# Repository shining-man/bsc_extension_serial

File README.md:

# Serial port extension for the BSC
This extension adds 8 additional serial ports to the Battery safety controller (BSC). This allows a total of 11 serial devices to be connected to the BSC.

The BSC is connected to this extension via an 8-pin bus cable.

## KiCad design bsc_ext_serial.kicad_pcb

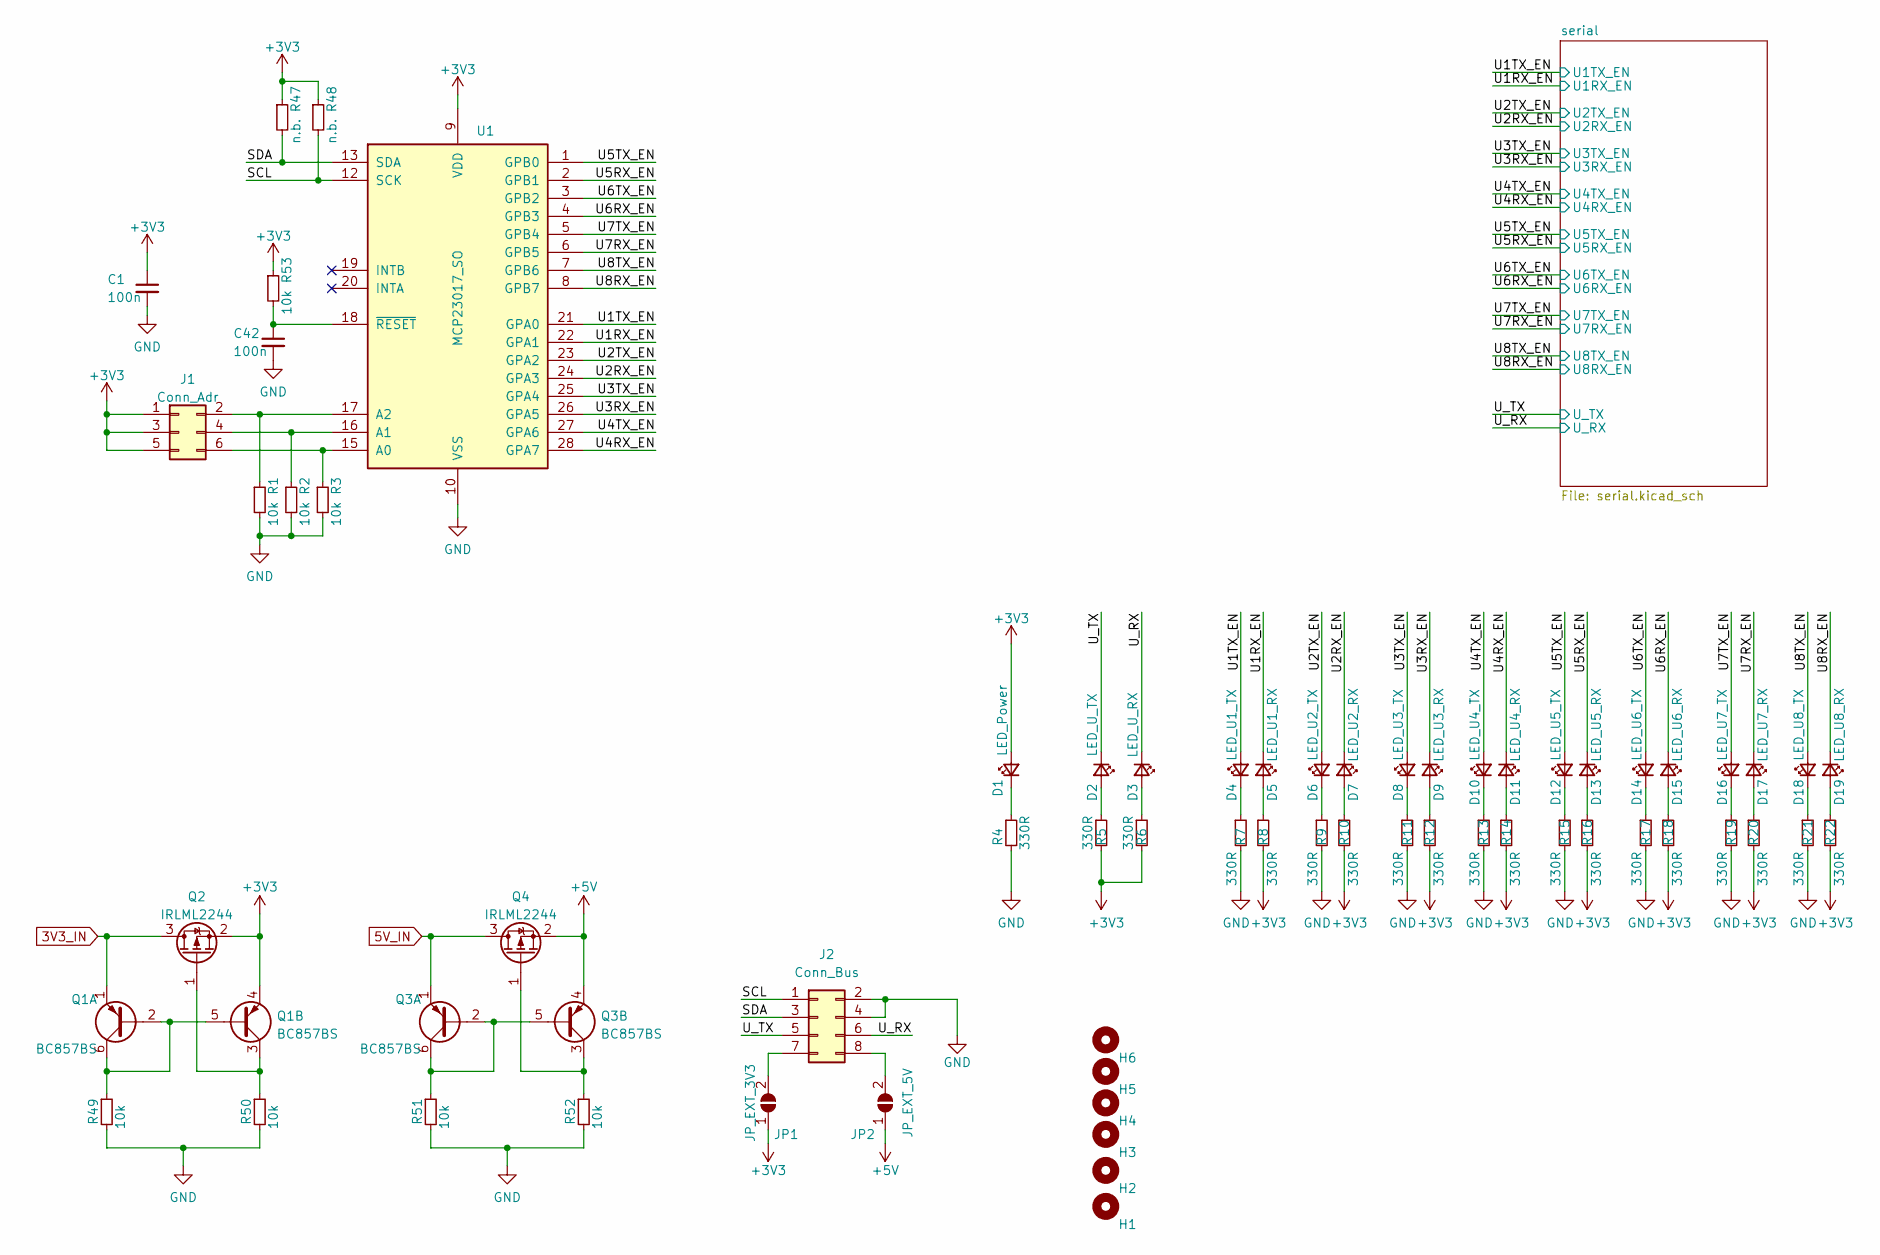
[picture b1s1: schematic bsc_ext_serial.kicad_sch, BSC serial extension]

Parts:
C1, C42: 100n; C_0603_1608Metric
D1: LED_Power; LED_0603_1608Metric
D2: LED_U_TX; LED_0603_1608Metric
D3: LED_U_RX; LED_0603_1608Metric
D4: LED_U1_TX; LED_0603_1608Metric
D5: LED_U1_RX; LED_0603_1608Metric
D6: LED_U2_TX; LED_0603_1608Metric
D7: LED_U2_RX; LED_0603_1608Metric
D8: LED_U3_TX; LED_0603_1608Metric
D9: LED_U3_RX; LED_0603_1608Metric
D10: LED_U4_TX; LED_0603_1608Metric
D11: LED_U4_RX; LED_0603_1608Metric
D12: LED_U5_TX; LED_0603_1608Metric
D13: LED_U5_RX; LED_0603_1608Metric
D14: LED_U6_TX; LED_0603_1608Metric
D15: LED_U6_RX; LED_0603_1608Metric
D16: LED_U7_TX; LED_0603_1608Metric
D17: LED_U7_RX; LED_0603_1608Metric
D18: LED_U8_TX; LED_0603_1608Metric
D19: LED_U8_RX; LED_0603_1608Metric
H1, H2, H3, H4, H5, H6: MountingHole; MountingHole_3.2mm_M3
J1: Conn_Adr; PinHeader_2x03_P2.54mm_Vertical
J2: Conn_Bus; PinHeader_2x04_P2.54mm_Vertical
JP1: JP_EXT_3V3; SolderJumper-2_P1.3mm_Open_RoundedPad1.0x1.5mm
JP2: JP_EXT_5V; SolderJumper-2_P1.3mm_Open_RoundedPad1.0x1.5mm
Q1, Q3: BC857BS; SOT-363_SC-70-6
Q2, Q4: IRLML2244; SOT-23
R1, R2, R3, R49, R50, R51, R52, R53: 10k; R_0603_1608Metric
R4, R5, R6, R7, R8, R9, R10, R11, R12, R13, R14, R15, R16, R17, R18, R19, R20, R21, R22: 330R; R_0603_1608Metric
R47, R48: n.b.; R_0603_1608Metric
U1: MCP23017_SO; SOIC-28W_7.5x17.9mm_P1.27mm

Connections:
3V3_IN: Q1.1 (E1), Q2.3 (D); also elsewhere on the board
5V_IN: Q3.1 (E1), Q4.3 (D); also elsewhere on the board
+3V3: C1.1, D1.2 (A), J1.1, J1.3, J1.5, JP1.1 (A), Q1.4 (E2), Q2.2 (S), R5.2, R6.2, R8.2, R10.2, R12.2, R14.2, R16.2, R18.2, R20.2, R22.2, R47.1, R48.1, R53.1, U1.9 (VDD); also elsewhere on the board
+5V: JP2.1 (A), Q3.4 (E2), Q4.2 (S); also elsewhere on the board
/SCL: J2.1, R48.2, U1.12 (SCK)
/SDA: J2.3, R47.2, U1.13 (SDA)
/U1RX_EN: D5.1 (K), U1.22 (GPA1); also elsewhere on the board
/U1TX_EN: D4.2 (A), U1.21 (GPA0); also elsewhere on the board
/U2RX_EN: D7.1 (K), U1.24 (GPA3); also elsewhere on the board
/U2TX_EN: D6.2 (A), U1.23 (GPA2); also elsewhere on the board
/U3RX_EN: D9.1 (K), U1.26 (GPA5); also elsewhere on the board
/U3TX_EN: D8.2 (A), U1.25 (GPA4); also elsewhere on the board
/U4RX_EN: D11.1 (K), U1.28 (GPA7); also elsewhere on the board
/U4TX_EN: D10.2 (A), U1.27 (GPA6); also elsewhere on the board
/U5RX_EN: D13.1 (K), U1.2 (GPB1); also elsewhere on the board
/U5TX_EN: D12.2 (A), U1.1 (GPB0); also elsewhere on the board
/U6RX_EN: D15.1 (K), U1.4 (GPB3); also elsewhere on the board
/U6TX_EN: D14.2 (A), U1.3 (GPB2); also elsewhere on the board
/U7RX_EN: D17.1 (K), U1.6 (GPB5); also elsewhere on the board
/U7TX_EN: D16.2 (A), U1.5 (GPB4); also elsewhere on the board
/U8RX_EN: D19.1 (K), U1.8 (GPB7); also elsewhere on the board
/U8TX_EN: D18.2 (A), U1.7 (GPB6); also elsewhere on the board
/U_RX: D3.1 (K), J2.6; also elsewhere on the board
/U_TX: D2.1 (K), J2.5; also elsewhere on the board
GND: C1.2, C42.2, J2.2, J2.4, R1.2, R2.2, R3.2, R4.2, R7.2, R9.2, R11.2, R13.2, R15.2, R17.2, R19.2, R21.2, R49.2, R50.2, R51.2, R52.2, U1.10 (VSS); also elsewhere on the board
unnamed: C42.1, R53.2, U1.18 (~RESET)
unnamed: D1.1 (K), R4.1
unnamed: D2.2 (A), R5.1
unnamed: D3.2 (A), R6.1
unnamed: D4.1 (K), R7.1
unnamed: D5.2 (A), R8.1
unnamed: D6.1 (K), R9.1
unnamed: D7.2 (A), R10.1
unnamed: D8.1 (K), R11.1
unnamed: D9.2 (A), R12.1
unnamed: D10.1 (K), R13.1
unnamed: D11.2 (A), R14.1
unnamed: D12.1 (K), R15.1
unnamed: D13.2 (A), R16.1
unnamed: D14.1 (K), R17.1
unnamed: D15.2 (A), R18.1
unnamed: D16.1 (K), R19.1
unnamed: D17.2 (A), R20.1
unnamed: D18.1 (K), R21.1
unnamed: D19.2 (A), R22.1
unnamed: J1.2, R1.1, U1.17 (A2)
unnamed: J1.4, R2.1, U1.16 (A1)
unnamed: J1.6, R3.1, U1.15 (A0)
unnamed: J2.7, JP1.2 (B)
unnamed: J2.8, JP2.2 (B)
unnamed: Q1.2 (B1), Q1.5 (B2), Q1.6 (C1), R49.1
unnamed: Q1.3 (C2), Q2.1 (G), R50.1
unnamed: Q3.2 (B1), Q3.5 (B2), Q3.6 (C1), R51.1
unnamed: Q3.3 (C2), Q4.1 (G), R52.1

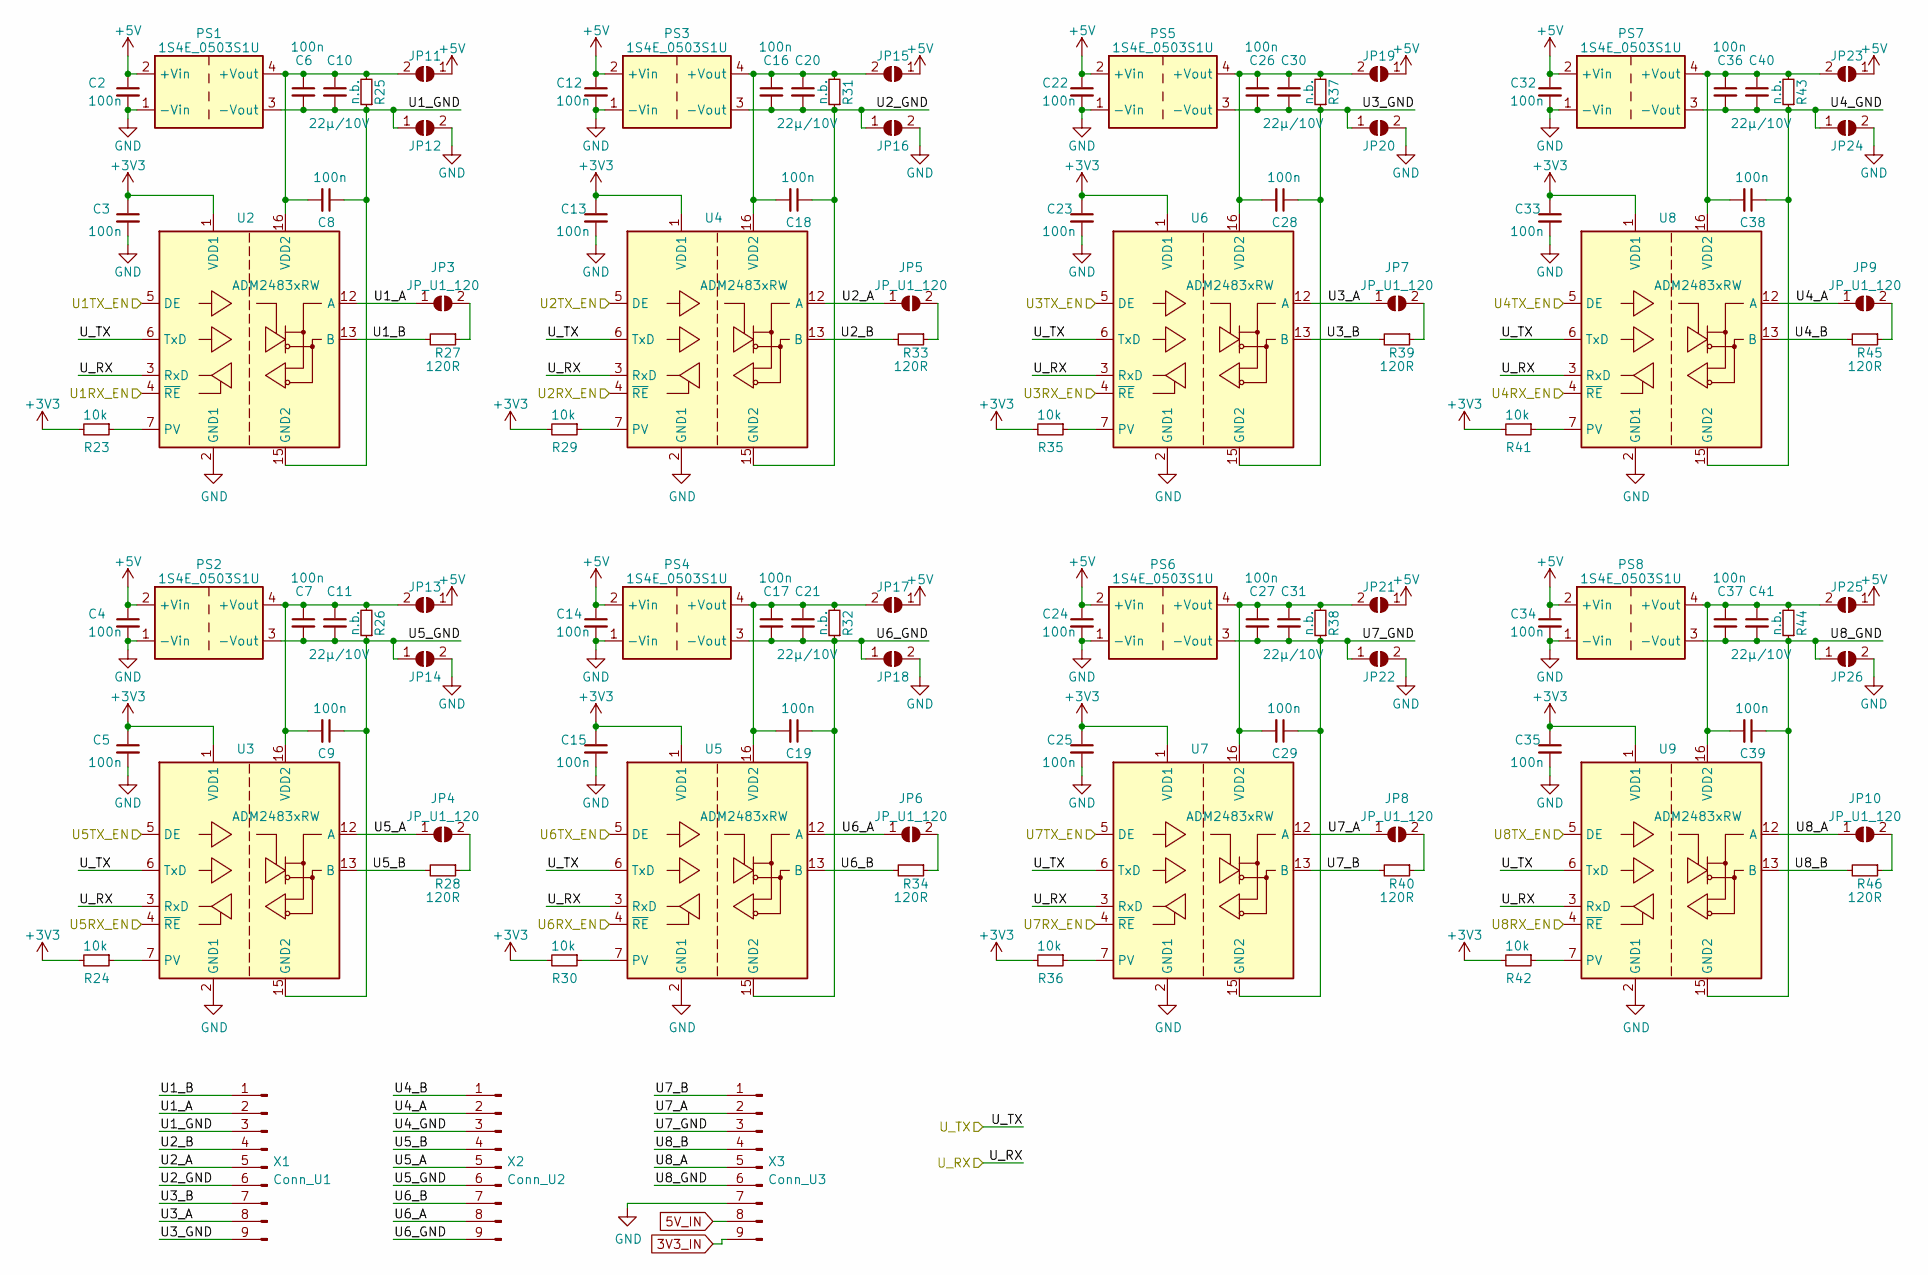
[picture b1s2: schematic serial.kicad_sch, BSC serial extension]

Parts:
C2, C3, C4, C5, C6, C7, C8, C9, C12, C13, C14, C15, C16, C17, C18, C19, C22, C23, C24, C25, C26, C27, C28, C29, C32, C33, C34, C35, C36, C37, C38, C39: 100n; C_0603_1608Metric
C10, C11, C20, C21, C30, C31, C40, C41: 22µ/10V; C_1206_3216Metric
JP3, JP4, JP5, JP6, JP7, JP8, JP9, JP10: JP_U1_120; SolderJumper-2_P1.3mm_Open_Pad1.0x1.5mm
JP11, JP12, JP13, JP14, JP15, JP16, JP17, JP18, JP19, JP20, JP21, JP22, JP23, JP24, JP25, JP26: SolderJumper-2_P1.3mm_Open_RoundedPad1.0x1.5mm
PS1, PS2, PS3, PS4, PS5, PS6, PS7, PS8: 1S4E_0503S1U; Converter_DCDC_GAPTEC_1S4E_S1U
R23, R24, R29, R30, R35, R36, R41, R42: 10k; R_0603_1608Metric
R25, R26, R31, R32, R37, R38, R43, R44: n.b.; R_0603_1608Metric
R27, R28, R33, R34, R39, R40, R45, R46: 120R; R_0603_1608Metric
U2, U3, U4, U5, U6, U7, U8, U9: ADM2483xRW; SOIC-16W_7.5x10.3mm_P1.27mm; PartNumber ADM2483BRWZ-REEL; LCSCStockCode C9637
X1: Conn_U1; PhoenixContact_MCV_1,5_9-G-3.81_1x09_P3.81mm_Vertical
X2: Conn_U2; PhoenixContact_MCV_1,5_9-G-3.81_1x09_P3.81mm_Vertical
X3: Conn_U3; PhoenixContact_MCV_1,5_9-G-3.81_1x09_P3.81mm_Vertical

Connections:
3V3_IN: X3.9; also elsewhere on the board
5V_IN: X3.8; also elsewhere on the board
+3V3: C3.1, C5.1, C13.1, C15.1, C23.1, C25.1, C33.1, C35.1, R23.2, R24.2, R29.2, R30.2, R35.2, R36.2, R41.2, R42.2, U2.1 (VDD1), U3.1 (VDD1), U4.1 (VDD1), U5.1 (VDD1), U6.1 (VDD1), U7.1 (VDD1), U8.1 (VDD1), U9.1 (VDD1); also elsewhere on the board
+5V: C2.1, C4.1, C12.1, C14.1, C22.1, C24.1, C32.1, C34.1, JP11.1 (A), JP13.1 (A), JP15.1 (A), JP17.1 (A), JP19.1 (A), JP21.1 (A), JP23.1 (A), JP25.1 (A), PS1.2 (+Vin), PS2.2 (+Vin), PS3.2 (+Vin), PS4.2 (+Vin), PS5.2 (+Vin), PS6.2 (+Vin), PS7.2 (+Vin), PS8.2 (+Vin); also elsewhere on the board
/U1RX_EN: U2.4 (~RE); also elsewhere on the board
/U1TX_EN: U2.5 (DE); also elsewhere on the board
/U2RX_EN: U4.4 (~RE); also elsewhere on the board
/U2TX_EN: U4.5 (DE); also elsewhere on the board
/U3RX_EN: U6.4 (~RE); also elsewhere on the board
/U3TX_EN: U6.5 (DE); also elsewhere on the board
/U4RX_EN: U8.4 (~RE); also elsewhere on the board
/U4TX_EN: U8.5 (DE); also elsewhere on the board
/U5RX_EN: U3.4 (~RE); also elsewhere on the board
/U5TX_EN: U3.5 (DE); also elsewhere on the board
/U6RX_EN: U5.4 (~RE); also elsewhere on the board
/U6TX_EN: U5.5 (DE); also elsewhere on the board
/U7RX_EN: U7.4 (~RE); also elsewhere on the board
/U7TX_EN: U7.5 (DE); also elsewhere on the board
/U8RX_EN: U9.4 (~RE); also elsewhere on the board
/U8TX_EN: U9.5 (DE); also elsewhere on the board
/U_RX: U2.3 (RxD), U3.3 (RxD), U4.3 (RxD), U5.3 (RxD), U6.3 (RxD), U7.3 (RxD), U8.3 (RxD), U9.3 (RxD); also elsewhere on the board
/U_TX: U2.6 (TxD), U3.6 (TxD), U4.6 (TxD), U5.6 (TxD), U6.6 (TxD), U7.6 (TxD), U8.6 (TxD), U9.6 (TxD); also elsewhere on the board
/serial/U1_A: JP3.1 (A), U2.12 (A), X1.2
/serial/U1_B: R27.2, U2.13 (B), X1.1
/serial/U1_GND: C6.2, C8.1, C10.2, JP12.1 (A), PS1.3 (-Vout), R25.1, U2.9 (GND2), U2.15 (GND2), X1.3
/serial/U2_A: JP5.1 (A), U4.12 (A), X1.5
/serial/U2_B: R33.2, U4.13 (B), X1.4
/serial/U2_GND: C16.2, C18.1, C20.2, JP16.1 (A), PS3.3 (-Vout), R31.1, U4.9 (GND2), U4.15 (GND2), X1.6
/serial/U3_A: JP7.1 (A), U6.12 (A), X1.8
/serial/U3_B: R39.2, U6.13 (B), X1.7
/serial/U3_GND: C26.2, C28.1, C30.2, JP20.1 (A), PS5.3 (-Vout), R37.1, U6.9 (GND2), U6.15 (GND2), X1.9
/serial/U4_A: JP9.1 (A), U8.12 (A), X2.2
/serial/U4_B: R45.2, U8.13 (B), X2.1
/serial/U4_GND: C36.2, C38.1, C40.2, JP24.1 (A), PS7.3 (-Vout), R43.1, U8.9 (GND2), U8.15 (GND2), X2.3
/serial/U5_A: JP4.1 (A), U3.12 (A), X2.5
/serial/U5_B: R28.2, U3.13 (B), X2.4
/serial/U5_GND: C7.2, C9.1, C11.2, JP14.1 (A), PS2.3 (-Vout), R26.1, U3.9 (GND2), U3.15 (GND2), X2.6
/serial/U6_A: JP6.1 (A), U5.12 (A), X2.8
/serial/U6_B: R34.2, U5.13 (B), X2.7
/serial/U6_GND: C17.2, C19.1, C21.2, JP18.1 (A), PS4.3 (-Vout), R32.1, U5.9 (GND2), U5.15 (GND2), X2.9
/serial/U7_A: JP8.1 (A), U7.12 (A), X3.2
/serial/U7_B: R40.2, U7.13 (B), X3.1
/serial/U7_GND: C27.2, C29.1, C31.2, JP22.1 (A), PS6.3 (-Vout), R38.1, U7.9 (GND2), U7.15 (GND2), X3.3
/serial/U8_A: JP10.1 (A), U9.12 (A), X3.5
/serial/U8_B: R46.2, U9.13 (B), X3.4
/serial/U8_GND: C37.2, C39.1, C41.2, JP26.1 (A), PS8.3 (-Vout), R44.1, U9.9 (GND2), U9.15 (GND2), X3.6
GND: C2.2, C3.2, C4.2, C5.2, C12.2, C13.2, C14.2, C15.2, C22.2, C23.2, C24.2, C25.2, C32.2, C33.2, C34.2, C35.2, JP12.2 (B), JP14.2 (B), JP16.2 (B), JP18.2 (B), JP20.2 (B), JP22.2 (B), JP24.2 (B), JP26.2 (B), PS1.1 (-Vin), PS2.1 (-Vin), PS3.1 (-Vin), PS4.1 (-Vin), PS5.1 (-Vin), PS6.1 (-Vin), PS7.1 (-Vin), PS8.1 (-Vin), U2.2 (GND1), U2.8 (GND1), U3.2 (GND1), U3.8 (GND1), U4.2 (GND1), U4.8 (GND1), U5.2 (GND1), U5.8 (GND1), U6.2 (GND1), U6.8 (GND1), U7.2 (GND1), U7.8 (GND1), U8.2 (GND1), U8.8 (GND1), U9.2 (GND1), U9.8 (GND1), X3.7; also elsewhere on the board
unnamed: C6.1, C8.2, C10.1, JP11.2 (B), PS1.4 (+Vout), R25.2, U2.16 (VDD2)
unnamed: C7.1, C9.2, C11.1, JP13.2 (B), PS2.4 (+Vout), R26.2, U3.16 (VDD2)
unnamed: C16.1, C18.2, C20.1, JP15.2 (B), PS3.4 (+Vout), R31.2, U4.16 (VDD2)
unnamed: C17.1, C19.2, C21.1, JP17.2 (B), PS4.4 (+Vout), R32.2, U5.16 (VDD2)
unnamed: C26.1, C28.2, C30.1, JP19.2 (B), PS5.4 (+Vout), R37.2, U6.16 (VDD2)
unnamed: C27.1, C29.2, C31.1, JP21.2 (B), PS6.4 (+Vout), R38.2, U7.16 (VDD2)
unnamed: C36.1, C38.2, C40.1, JP23.2 (B), PS7.4 (+Vout), R43.2, U8.16 (VDD2)
unnamed: C37.1, C39.2, C41.1, JP25.2 (B), PS8.4 (+Vout), R44.2, U9.16 (VDD2)
unnamed: JP3.2 (B), R27.1
unnamed: JP4.2 (B), R28.1
unnamed: JP5.2 (B), R33.1
unnamed: JP6.2 (B), R34.1
unnamed: JP7.2 (B), R39.1
unnamed: JP8.2 (B), R40.1
unnamed: JP9.2 (B), R45.1
unnamed: JP10.2 (B), R46.1
unnamed: R23.1, U2.7 (PV)
unnamed: R24.1, U3.7 (PV)
unnamed: R29.1, U4.7 (PV)
unnamed: R30.1, U5.7 (PV)
unnamed: R35.1, U6.7 (PV)
unnamed: R36.1, U7.7 (PV)
unnamed: R41.1, U8.7 (PV)
unnamed: R42.1, U9.7 (PV)

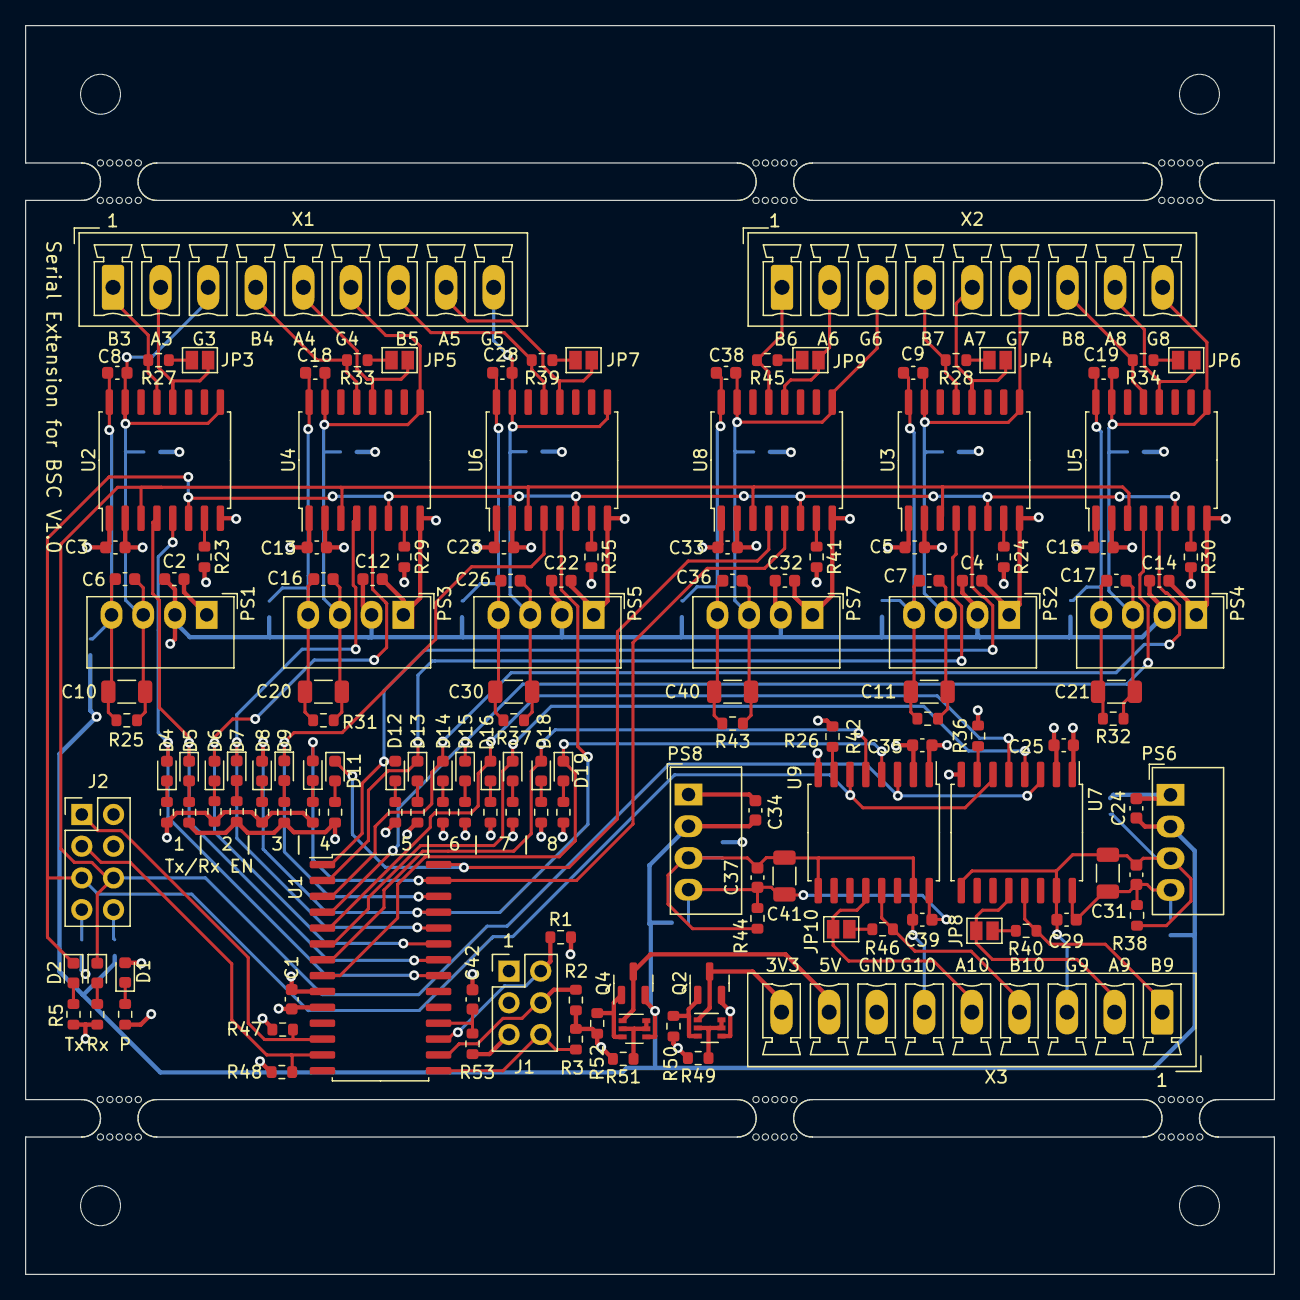
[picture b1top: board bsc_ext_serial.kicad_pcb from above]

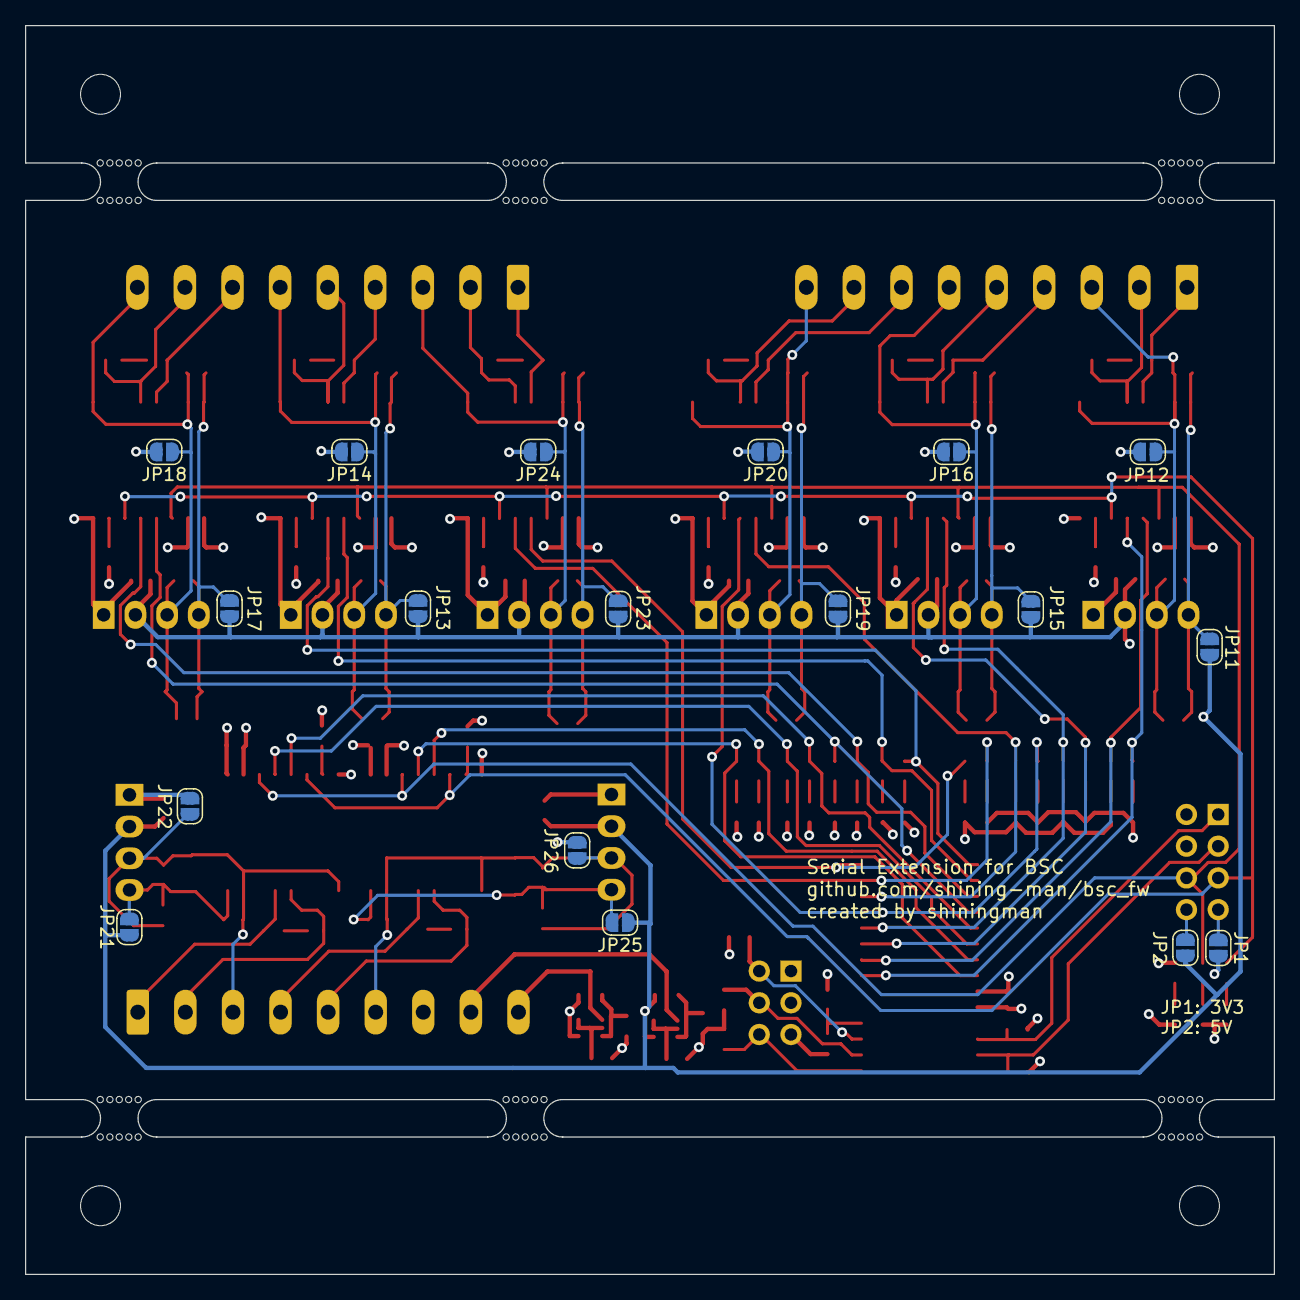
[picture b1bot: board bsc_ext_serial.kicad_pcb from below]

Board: 4 copper layers, 100.0 x 100.0 mm, 176 parts (18 on the bottom side), 102 nets.

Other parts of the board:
mouse-bite-3mm-slot_1, mouse-bite-3mm-slot_2, mouse-bite-3mm-slot_3, mouse-bite-3mm-slot_4, mouse-bite-3mm-slot_5, mouse-bite-3mm-slot_6: VAL**; mouse-bite-3mm-slot

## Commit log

2023-04-01 First revision
2023-04-03 modify J2 position
